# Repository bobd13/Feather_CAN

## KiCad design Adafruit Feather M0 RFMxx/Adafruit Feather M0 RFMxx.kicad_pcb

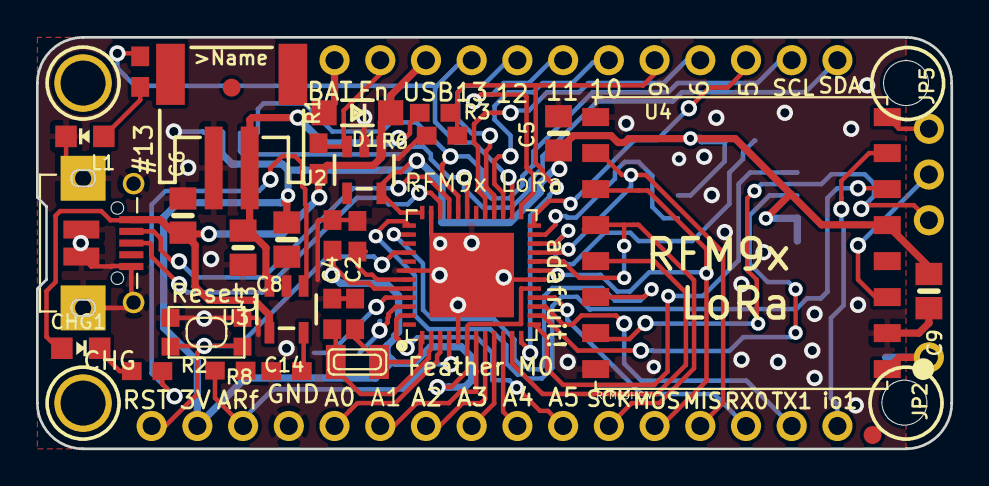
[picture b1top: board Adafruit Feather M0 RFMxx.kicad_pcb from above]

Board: 2 copper layers, 50.8 x 22.9 mm, 43 parts (0 on the bottom side), 50 nets.

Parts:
C1, C7, C14: 1uF; 0603-NO
C2, C4: 22pF; 0603-NO
C3, C6, C8: 10µF; 0805-NO
C5, C9: 10uF; 0805-NO
CHG1: ORANGE; CHIPLED_0805_NOOUTLINE
D1: MBR120; SOD-123
JP1: HEADER-1X16ROUND; 1X16_ROUND
JP2: HEADER-1X1ROUND; 1X01_ROUND
JP3: HEADER-1X12; 1X12_ROUND
JP5: HEADER-1X3ROUND; 1X03_ROUND
JP7: SM04B-SRSS-TB(LF)(SN); SM04B-SRSS-TB(LFSN)
L1: RED; CHIPLED_0805_NOOUTLINE
R1, R3: 100k; 0603-NO
R2: 1K; 0603-NO
R4: 10K; 0603-NO
R6: 100K; 0603-NO
R7: 2.2K; 0603-NO
R8: 10K\; 0603-NO
SW1: SPST_TACT-KMR2; KMR2
TP1, TP2: TESTPOINTROUND1.5MM; TESTPOINT_ROUND_1.5MM
U1: 2MB Flash; SOIC8_208MIL
U2: AP2112K-3.3; SOT23-5
U3: MCP73831T-2ACI/OT; SOT23-5
U4: RFM69HCW; RFMHCW_SMT
U$4: ATSAMD21G18_QFN; TQFN48_7MM
U$31, U$31#2, U$31#3, U$32: MOUNTINGHOLE2.5; MOUNTINGHOLE_2.5_PLATED
U$34, U$35: FIDUCIAL; FIDUCIAL_1MM
X1: JSTPH; JSTPH2
X2: 32.768; XTAL3215
X3: microUSB; 4UCONN_20329_V2
X4: uFL; U.FL

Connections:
+3V3: C5.1, C7.1, C8.1, C9.1, JP1.15, JP7.2, R4.2, U1.3, U1.7, U1.8, U2.5, U4.5P, U$4.6, U$4.17, U$4.36, U$4.44
/A0: JP1.12, U$4.3
/A1: JP1.11, U$4.7
/A2: JP1.10, U$4.8
/A3: JP1.9, U$4.9
/A4: JP1.8, U$4.10
/A5: JP1.7, U$4.47
/AREF: C14.1, JP1.14, U$4.4
/D0: JP1.3, U$4.16
/D1: JP1.2, U$4.15
/D2_FLASHMISO: U1.2, U$4.23
/D3_FLASHSCK: U1.6, U$4.14
/D4_FLASHMOSI: U1.5, U$4.13
/D5: JP3.10, U$4.24
/D6: JP3.9, U$4.29
/D8_CS: U4.13P, U$4.11
/D9: JP3.8, R3.2, R6.1, U$4.12
/D10: JP3.7, U$4.27
/D11: JP3.6, U$4.25
/D12: JP3.5, U$4.28
/D13: JP3.4, R7.1, U$4.26
/D+: U$4.34, X3.D+
/D-: U$4.33, X3.D-
/DIO1: JP1.1, U4.7P
/DIO2: JP5.3, U4.8P
/DIO3: JP5.2, U4.3P
/DIO5: JP5.1, U4.15P
/EN: JP3.2, R1.2, U2.3
/FLASH_CS: R4.1, U1.1, U$4.22
/MISO: JP1.4, U4.10P, U$4.21
/MOSI: JP1.5, U4.11P, U$4.19
/RXD_IRQ: U4.6P, U$4.37
/SCK: JP1.6, U4.12P, U$4.20
/SCL: JP3.11, JP7.4, U$4.32
/SDA: JP3.12, JP7.3, U$4.31
/SWCLK: TP1.P$1, U$4.45
/SWDIO: TP2.P$1, U$4.46
/TXD_RST: U4.14P, U$4.38
/~RESET: JP1.16, SW1.1, SW1.3, U$4.40
GND: C1.2, C2.2, C3.2, C4.2, C5.2, C6.2, C7.2, C8.2, C9.2, C14.2, JP1.13, JP7.1, L1.C, R6.2, R8.2, SW1.2, SW1.4, U1.4, U2.2, U3.2, U4.2P, U4.9P, U4.16P, U$4.5, U$4.18, U$4.35, U$4.42, U$4.THERMAL, X1.1, X3.BASE@1, X3.BASE@2, X3.GND, X3.SPRT@1, X3.SPRT@2, X3.SPRT@3, X3.SPRT@4, X4.1, X4.2
unnamed: C1.1, U$4.43
unnamed: C2.1, U$4.1, X2.P$1
unnamed: C4.1, U$4.2, X2.P$2
unnamed: CHG1.C, R2.1
unnamed: JP2.1, U4.1P, X4.3
unnamed: L1.A, R7.2
unnamed: R2.2, U3.1
unnamed: R8.1, U3.5
VBAT: C3.1, D1.A, JP3.1, R3.1, U3.3, X1.2
VBUS: C6.1, CHG1.A, D1.C, JP3.3, R1.1, U2.1, U3.4, X3.VBUS

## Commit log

2018-12-28 Kicad import of Eagle project
2018-12-28 Plotting gerbers caused ground fill to occur first - defined area outlines were already there, just not the fill.
2018-12-29 Started adding qwiic connector.
2018-12-29 Qwiic connector addition completed
2019-01-03 Took a look at fitting in via's needed to breakout pins 22 & 23. Looks like it can be done without a lot of work. Likely will need to shrink a couple of existing via's.
    DRC complained about some things that haven't changed from the original Adafruit
    design (USB connector mounting holes too close to something, and maybe something
    else.
2019-01-03 Add gerbers - will need to be run again after further fixes.
    Ran DRC - 2 holes as part of micro-USB have errors - just ignore.
    Total of 3 errors - holes too close to pads (2) and track too close to hole.
    Still complaining about 2 missing connections.
2019-01-06 Moving silscreen around and made some invisible. Working on a track near 144, 100.
2019-01-06 Found cause of GND airwire around 144,100: ground pour on bottom was interrupted by routing of i2c to qwiic connector. Moving it to allow GND to connect eliminated issue.
    Still have complaint about TOP and BOTTOM GND pours not connected.
2019-01-06 Draw gerbers
2019-01-07 Remaining Air wire was caused by ground pour on bottom that had become an island with the addition of the qwiic connector. Rerouted signals in that area to allow it to reconnect with other ground pou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
    Now only "not connected" are defined ground area top and bottom.
    Added gnd track between voltage sense resistor divider and ground so that it
    shows when highlighting the GND net.
    Moved track within USB connector to eliminate DRC "track too close to ..." error.
    Now only 2 DRC errors are with holes in PCB that are part of X3 (USB connector).
    Cleaned up silkscreen.
2019-01-07 Added routing and vias to get SAMD21 pins 23 and 24 routed.
2019-01-07 Added SPI flash from Adafruit Feather M0 Express. Still need to: - change 2 connections to RFM to other available pins - connect flash in schematic - route Note: the Netlist import complained about c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
2019-01-07 Maybe in last commit: - Added spi flash footprint from Adafruit Feather M0 Express. - changed footprint of imported resistor for SPI flash to same as other 0603's.
    Removed extraneous small track on SDA on TOP.
2019-01-08 Before moving runners around for room for new traces.
2019-01-08 New RST and IRQ lines chosen for RFM. Everything routed. DRC errors still to be fixed.
2019-01-09 Ran BOM generator. Errors on "U$34".
2019-01-09 Solution for component designators that start with "U$": Created copy of the xml output of Generate BOM and changed all "U$.." to "US.." and ran the python program from the command line and it works 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
2019-01-09 Fixed DRC errors. Remaining are ignores? - 2 pads part of USB connector - Top and Bottom regions not connected
2019-01-10 Fixed silscreen: - move bottom silk away from flash chip - change minimum silkscreen text width to 0.1524 mm (0.6mil) to match jlcpcb capability
    Note:
    Could not move silkscreen polygon that was for Node # - cannot seem to select it
2019-01-11 Could not select polygon on bottom silk, so manually deleted from kicad_pcb file. Re-ran Gerbers. Noticed 2 mounting holes are missing.
2019-01-11 This is version 0.1 of qwiic and flash board.
2019-01-11 Parts mostly added. Need to confirm footprints. Before eliminating RFM parts.
2019-01-11 Eliminated RFM and associated parts. Started to place and route. Must still confirm footprints.
2019-01-12 Generated BOM.
2019-01-12 Routing ...
2019-01-13 Routed, with some remaining errors: - some grounds disconnected - odd error about runner on PAD25 of MCP too close to PAD24. But there is no runner on PAD25 - just the footprint itself.
2019-01-13 On MCP25625, added connection from STBY to GND to put device in Normal mode.
2019-01-14 Fix mounting hole. Update silscreen.
2019-01-14 Remove extraneous "D2" silkscreen (from RFM).
2019-01-14 Fix mounting hole footprint.
2019-03-17 BD - Not sure what changed besides creating gerbers and plots
2020-02-19 Add arduino directory with board files for Arduino board manager.
2020-02-19 Fixed file names.
2020-02-19 Attempting to get link right.
2020-02-19 Missing comma in package json file
2020-02-19 Still trying to fix json parsing error ...
2020-02-19 Now trying to find java null pointer in package json file
2021-02-01 Not sure what the changes are in fp-info-cache (only changed file), but committing.
